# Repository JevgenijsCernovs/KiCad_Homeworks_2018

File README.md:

# KiCad_Homeworks_2018
Jevgenijs Cernovs 2IZB

Si izveidota repozitorija paredzeta kursa darbiem un projektiem ar PCB.

				2017/2018 m.g.

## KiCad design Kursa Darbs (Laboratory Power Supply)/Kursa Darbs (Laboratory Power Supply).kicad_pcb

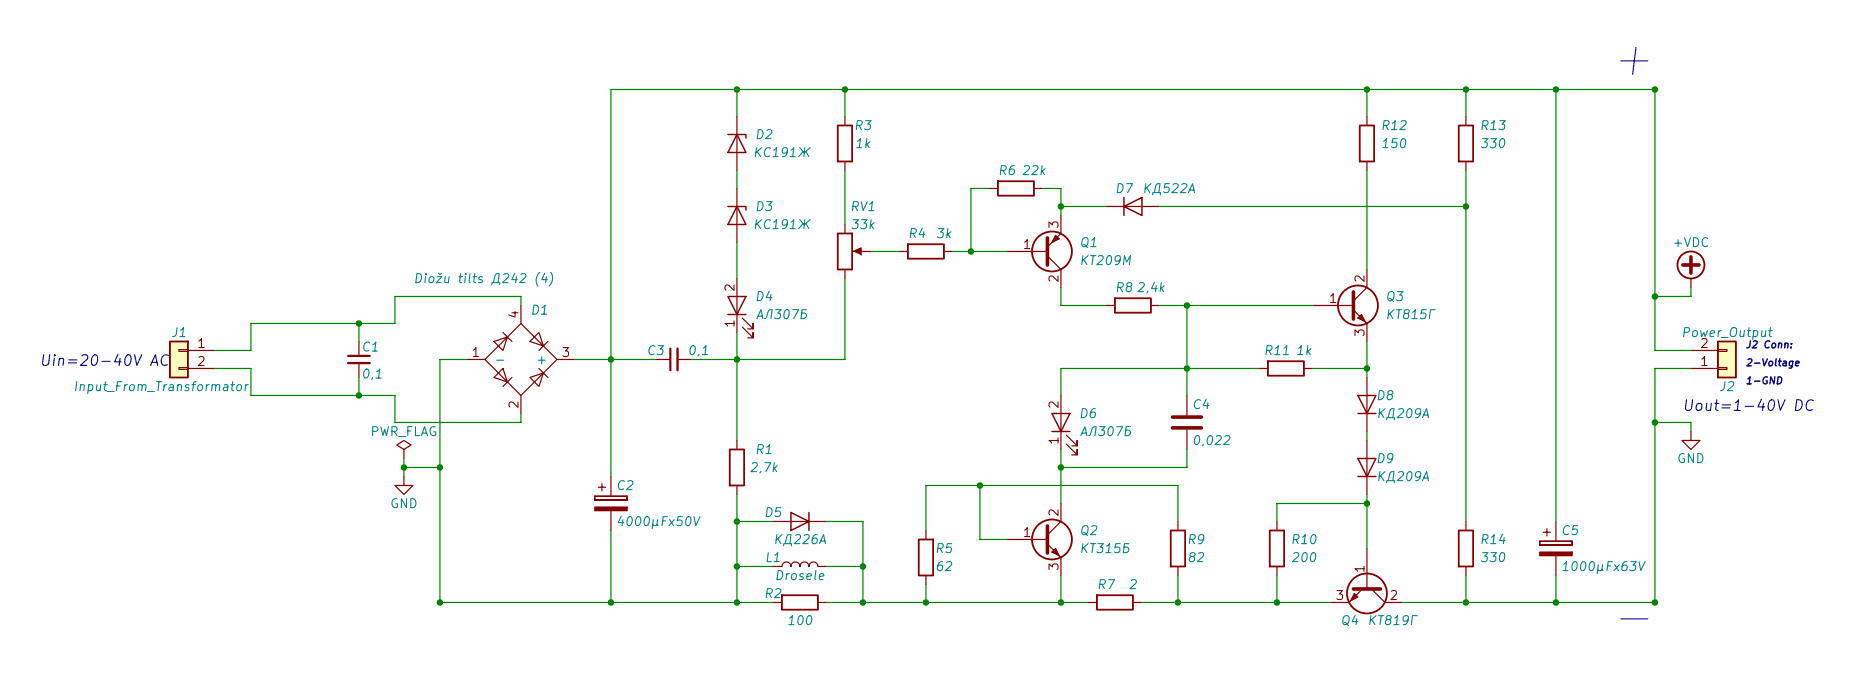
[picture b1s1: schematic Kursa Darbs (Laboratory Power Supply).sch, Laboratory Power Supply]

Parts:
C1, C3: 0,1; C_Disc_D6.0mm_W2.5mm_P5.00mm
C2: 4000µFx50V; CP_Radial_D40.0mm_P10.00mm_SnapIn
C4: 0,022; C_Disc_D4.7mm_W2.5mm_P5.00mm
C5: 1000µFx63V; CP_Radial_D12.5mm_P7.50mm
D1: Diožu tilts Д242 (4); Diode_Bridge_18.5x5.5
D2, D3: КС191Ж; D_DO-15_P15.24mm_Horizontal
D4, D6: АЛ307Б; LED_D5.0mm
D5: КД226А; D_DO-41_SOD81_P10.16mm_Horizontal
D7: КД522А; D_DO-41_SOD81_P10.16mm_Horizontal
D8, D9: КД209А; D_DO-41_SOD81_P10.16mm_Horizontal
J1: Input_From_Transformator; Banana_Jack_2Pin
J2: Power_Output; Banana_Jack_2Pin
L1: Drosele; L_Axial_L30.0mm_D8.0mm_P35.56mm_Horizontal_Fastron_77A
Q1: КТ209М; TO-92_Inline_Wide
Q2: КТ315Б; TO-39-3
Q3: КТ815Г; TO-126_Vertical
Q4: КТ819Г; TO-220-3_Vertical
R1: 2,7k; R_Axial_DIN0309_L9.0mm_D3.2mm_P20.32mm_Horizontal
R2: 100; R_Axial_DIN0207_L6.3mm_D2.5mm_P15.24mm_Horizontal
R3, R11: 1k; R_Axial_DIN0207_L6.3mm_D2.5mm_P15.24mm_Horizontal
R4: 3k; R_Axial_DIN0207_L6.3mm_D2.5mm_P15.24mm_Horizontal
R5: 62; R_Axial_DIN0207_L6.3mm_D2.5mm_P15.24mm_Horizontal
R6: 22k; R_Axial_DIN0207_L6.3mm_D2.5mm_P15.24mm_Horizontal
R7: 2; R_Axial_Power_L20.0mm_W6.4mm_P30.48mm
R8: 2,4k; R_Axial_DIN0207_L6.3mm_D2.5mm_P15.24mm_Horizontal
R9: 82; R_Axial_DIN0207_L6.3mm_D2.5mm_P15.24mm_Horizontal
R10: 200; R_Axial_DIN0207_L6.3mm_D2.5mm_P15.24mm_Horizontal
R12: 150; R_Axial_DIN0516_L15.5mm_D5.0mm_P25.40mm_Horizontal
R13, R14: 330; R_Axial_DIN0516_L15.5mm_D5.0mm_P25.40mm_Horizontal
RV1: 33k; Potentiometer_Omeg_PC16PU_Horizontal

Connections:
+VDC: C2.1, C3.1, C5.1, D1.3 (+), D2.1 (K), J2.2, R3.1, R12.1, R13.1
GND: C2.2, C5.2, D1.1 (-), D5.2 (A), J2.1, L1.1, Q4.2 (C), R1.2, R2.2, R14.2
unnamed: C1.1, D1.4, J1.1
unnamed: C1.2, D1.2, J1.2
unnamed: C3.2, D4.1 (K), R1.1, RV1.3
unnamed: C4.1, D6.2 (A), Q3.1 (B), R8.1, R11.2
unnamed: C4.2, D6.1 (K), Q2.2 (C)
unnamed: D2.2 (A), D3.1 (K)
unnamed: D3.2 (A), D4.2 (A)
unnamed: D5.1 (K), L1.2, Q2.3 (E), R2.1, R5.1, R7.2
unnamed: D7.1 (K), Q1.3 (E), R6.1
unnamed: D7.2 (A), R13.2, R14.1
unnamed: D8.1 (K), D9.2 (A)
unnamed: D8.2 (A), Q3.3 (E), R11.1
unnamed: D9.1 (K), Q4.1 (B), R10.1
unnamed: Q1.1 (B), R4.1, R6.2
unnamed: Q1.2 (C), R8.2
unnamed: Q2.1 (B), R5.2, R9.1
unnamed: Q3.2 (C), R12.2
unnamed: Q4.3 (E), R7.1, R9.2, R10.2
unnamed: R3.2, RV1.1
unnamed: R4.2, RV1.2

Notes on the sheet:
Uin=20-40V AC
Uout=1-40V DC
2-Voltage
1-GND
J2 Conn:

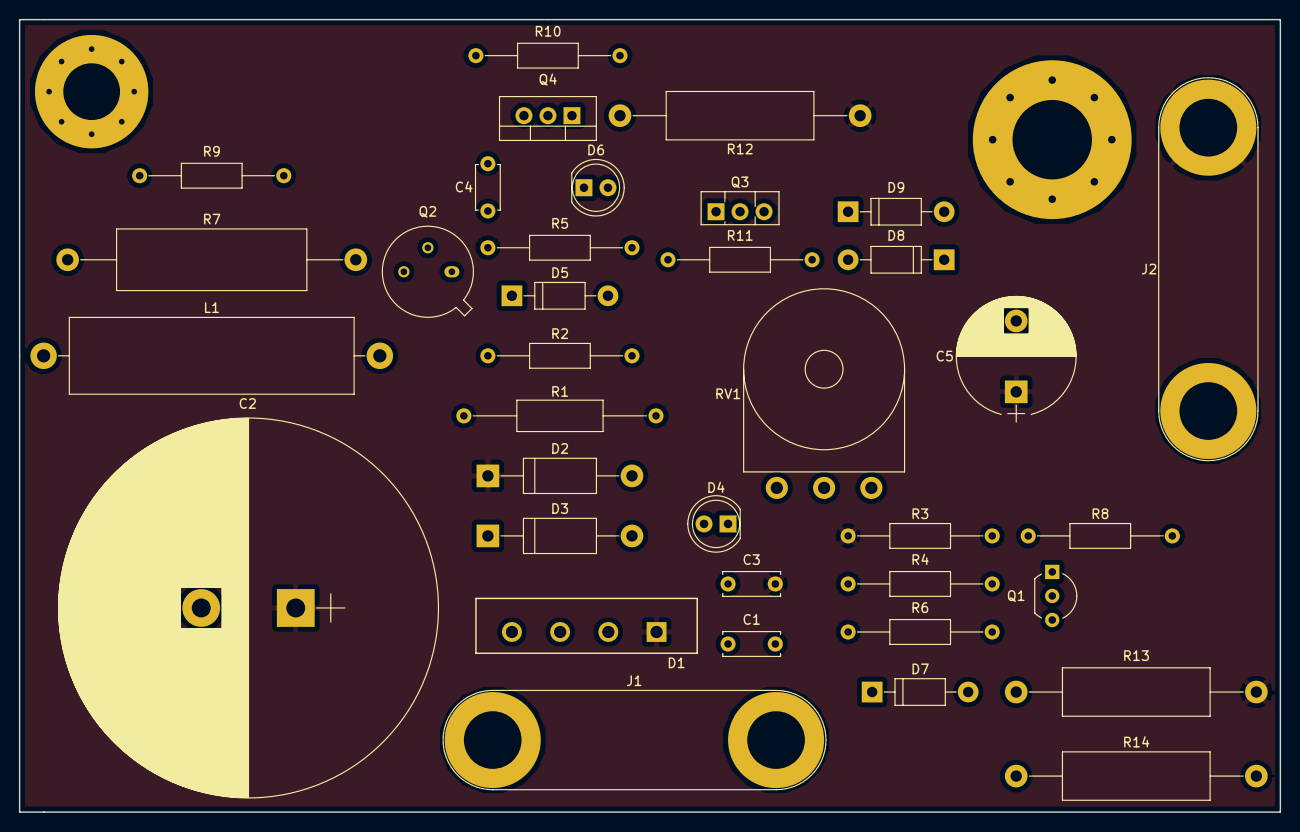
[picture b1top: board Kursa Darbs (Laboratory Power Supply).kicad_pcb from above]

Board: 4 copper layers, 133.4 x 83.8 mm, 36 parts (0 on the bottom side), 22 nets.

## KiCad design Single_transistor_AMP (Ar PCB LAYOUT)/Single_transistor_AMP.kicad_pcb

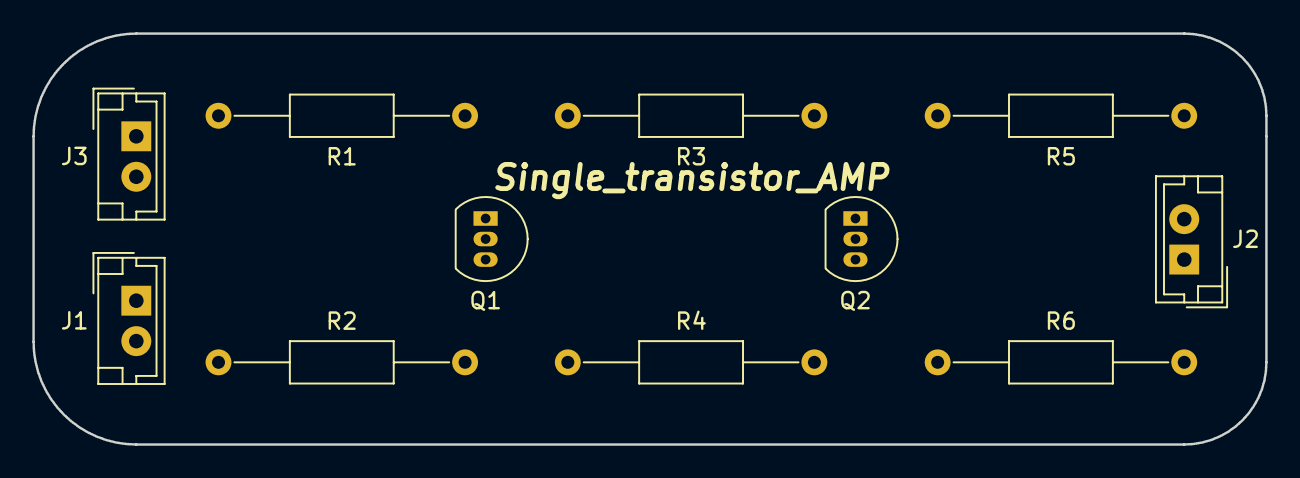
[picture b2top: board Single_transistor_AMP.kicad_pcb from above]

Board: 2 copper layers, 76.2 x 25.4 mm, 11 parts (0 on the bottom side), 7 nets, no tracks yet.

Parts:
J1: Signal_In; JST_EH_B02B-EH-A_02x2.50mm_Straight
J2: Signal_Out; JST_EH_B02B-EH-A_02x2.50mm_Straight
J3: PWN_Conn; JST_EH_B02B-EH-A_02x2.50mm_Straight
Q1, Q2: BC548; TO-92_Inline_Narrow_Oval
R1: 33k; R_Axial_DIN0207_L6.3mm_D2.5mm_P15.24mm_Horizontal
R2, R3: 6k8; R_Axial_DIN0207_L6.3mm_D2.5mm_P15.24mm_Horizontal
R4: 1k; R_Axial_DIN0207_L6.3mm_D2.5mm_P15.24mm_Horizontal
R5: 820; R_Axial_DIN0207_L6.3mm_D2.5mm_P15.24mm_Horizontal
R6: 470; R_Axial_DIN0207_L6.3mm_D2.5mm_P15.24mm_Horizontal

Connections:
+12V: J3.1, R1.1, R3.1, R5.1
GND: J1.2, J2.1, J3.2, R2.2, R4.2, R6.2
unnamed: J1.1, Q1.2, R1.2, R2.1
unnamed: J2.2, Q2.1, R5.2
unnamed: Q1.1, Q2.2, R3.2
unnamed: Q1.3, R4.1
unnamed: Q2.3, R6.1

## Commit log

2018-02-16 README 1. majas darbs
2018-02-16 README.md HOMEWORK CHECK
2018-03-11 J_Cernovs_MultiVib
2018-03-13 J_Cernovs_MultiVib (Izlabotais darbs)
2018-03-15 Single_transistor_AMP
2018-03-18 PWR_Supply
2018-03-25 Battery
2018-03-30 PWR_Supply (Izlabotais darbs)
2018-03-31 Single_transistor_AMP (Ar PCBNEW)
2018-04-08 Single_transistor_AMP (Ar PCB LAYOUT)
2018-04-29 Single_transistor_AMP (Ar ROUTING un FILLED ZONES)
2018-05-02 Single_transistor_AMP(Gerbers And Drills)
2018-05-03 Single_transistor_AMP_SVG_And_BOM_Files
2018-05-08 Component_Homework(JevgēņijsČernovs2IZB)
2018-06-11 Kursa Darbs (Laboratory Power Supply)
